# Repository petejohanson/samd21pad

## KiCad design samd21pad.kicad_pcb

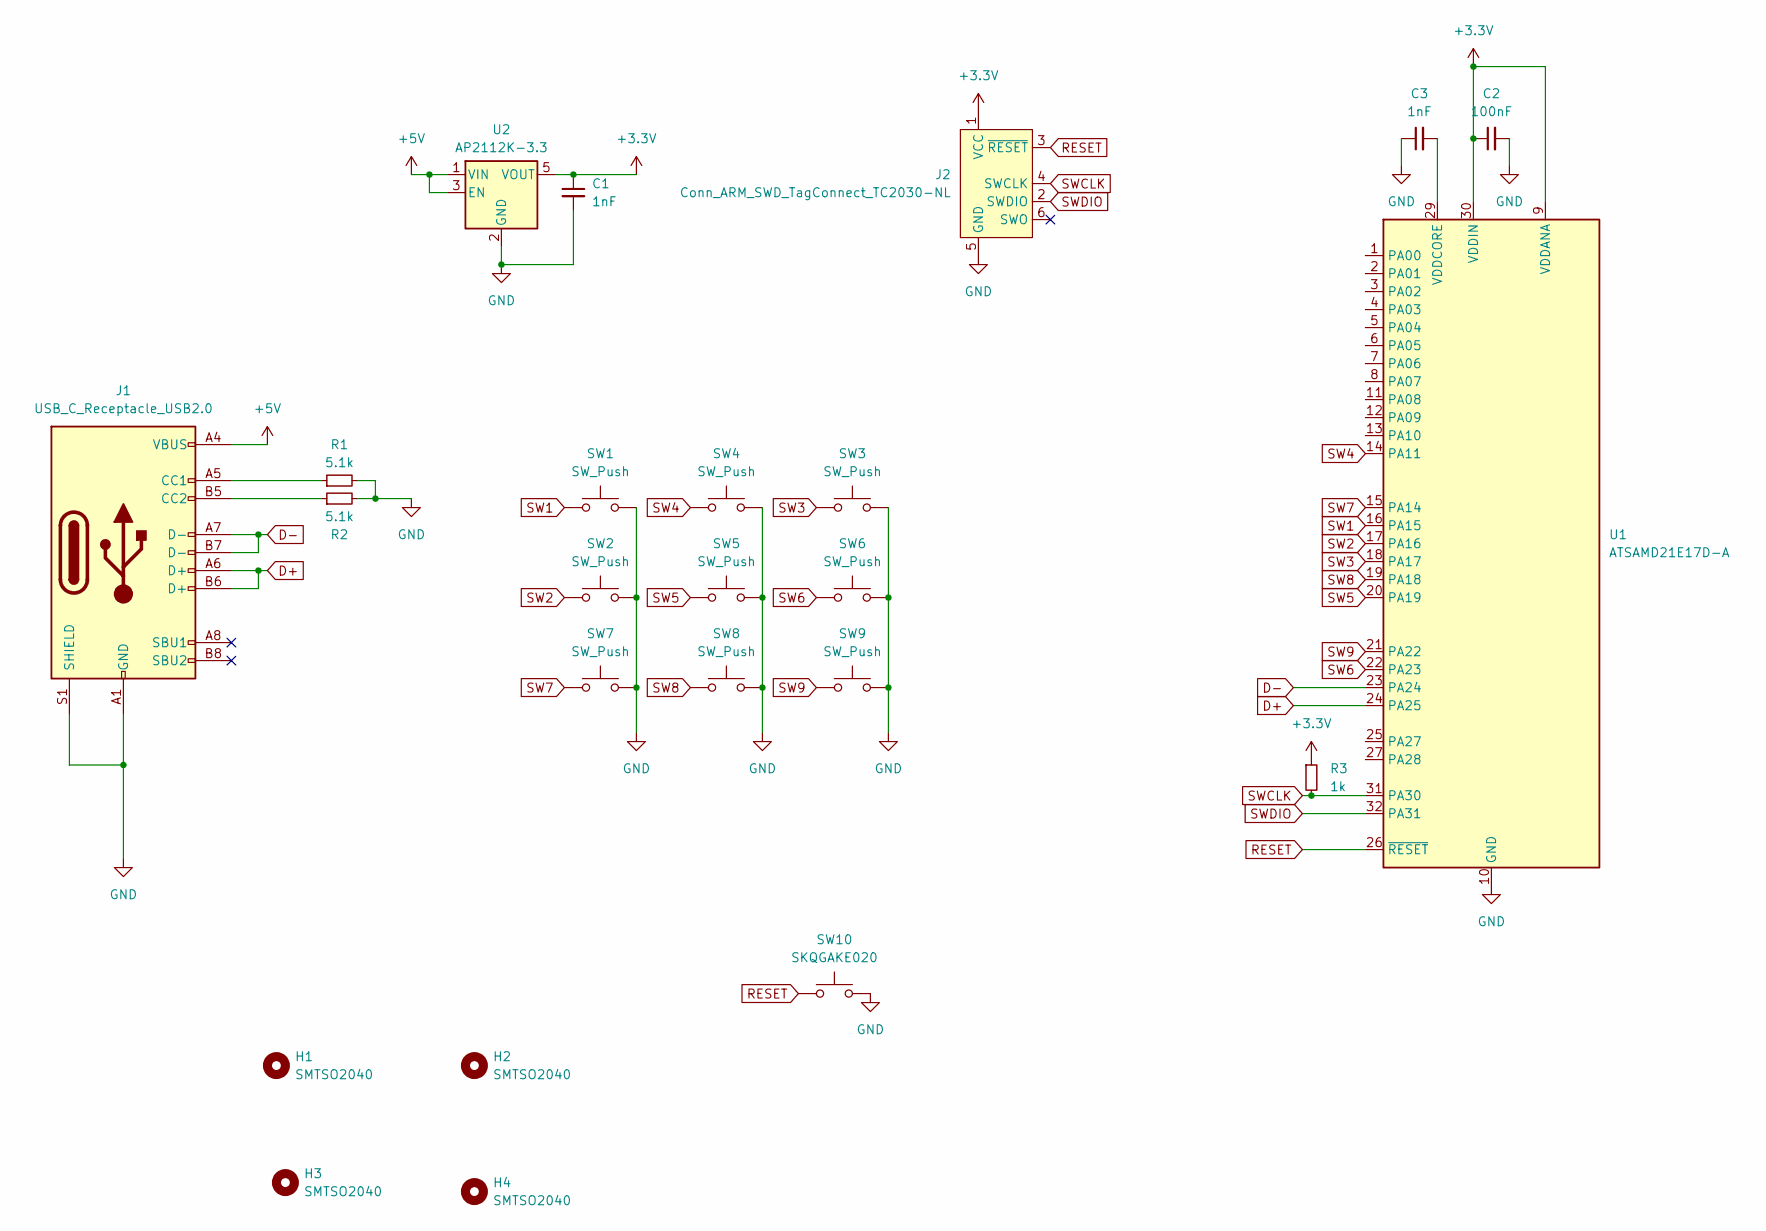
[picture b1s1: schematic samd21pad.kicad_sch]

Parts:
C1, C3: 1nF; C_0805_2012Metric; LCSC Part Number C129637
C2: 100nF; C_0805_2012Metric; LCSC Part Number C2169363
H1, H2, H3, H4: SMTSO2040; MountingHole_M2_Pad_NonPTH_TopOnly; LCSC Part Number C2916349
J1: USB_C_Receptacle_USB2.0; USB_C_Receptacle_GT-USB-7010; LCSC Part Number C3001293
J2: Conn_ARM_SWD_TagConnect_TC2030-NL; Tag-Connect_TC2030-IDC-NL_2x03_P1.27mm_Vertical
R1, R2: 5.1k; R_0805_2012Metric
R3: 1k; R_0805_2012Metric
SW1, SW2, SW3, SW4, SW5, SW6, SW7, SW8, SW9: SW_Push; SW_MX_1u
SW10: SKQGAKE020; SW_SPST_SKQG_WithStem; MPN SKQGAKE020; LCSC Part Number C388858
U1: ATSAMD21E17D-A; TQFP-32_7x7mm_P0.8mm; MPN ATSAMD21E17D-A
U2: AP2112K-3.3; SOT-23-5; MPN AP2112K-3.3; LCSC Part Number C3021085

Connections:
+3.3V: C1.1, C2.1, J2.1 (VCC), R3.1, U1.9 (VDDANA), U1.30 (VDDIN), U2.5 (VOUT)
+5V: J1.A4 (VBUS), J1.A9 (VBUS), J1.B4 (VBUS), J1.B9 (VBUS), U2.1 (VIN), U2.3 (EN)
D+: J1.A6 (D+), J1.B6 (D+), U1.24 (PA25)
D-: J1.A7 (D-), J1.B7 (D-), U1.23 (PA24)
GND: C1.2, C2.2, C3.1, J1.A1 (GND), J1.A12 (GND), J1.B1 (GND), J1.B12 (GND), J1.S1 (SHIELD), J2.5 (GND), R1.2, R2.2, SW1.2, SW2.2, SW3.2, SW4.2, SW5.2, SW6.2, SW7.2, SW8.2, SW9.2, SW10.2, U1.10 (GND), U1.28 (GND), U2.2 (GND)
unnamed: J1.A5 (CC1), R1.1
unnamed: J1.B5 (CC2), R2.1
unnamed: C3.2, U1.29 (VDDCORE)
RESET: J2.3 (~RESET), SW10.1, U1.26 (~RESET)
SW1: SW1.1, U1.16 (PA15)
SW2: SW2.1, U1.17 (PA16)
SW3: SW3.1, U1.18 (PA17)
SW4: SW4.1, U1.14 (PA11)
SW5: SW5.1, U1.20 (PA19)
SW6: SW6.1, U1.22 (PA23)
SW7: SW7.1, U1.15 (PA14)
SW8: SW8.1, U1.19 (PA18)
SW9: SW9.1, U1.21 (PA22)
SWCLK: J2.4 (SWCLK), R3.2, U1.31 (PA30)
SWDIO: J2.2 (SWDIO), U1.32 (PA31)

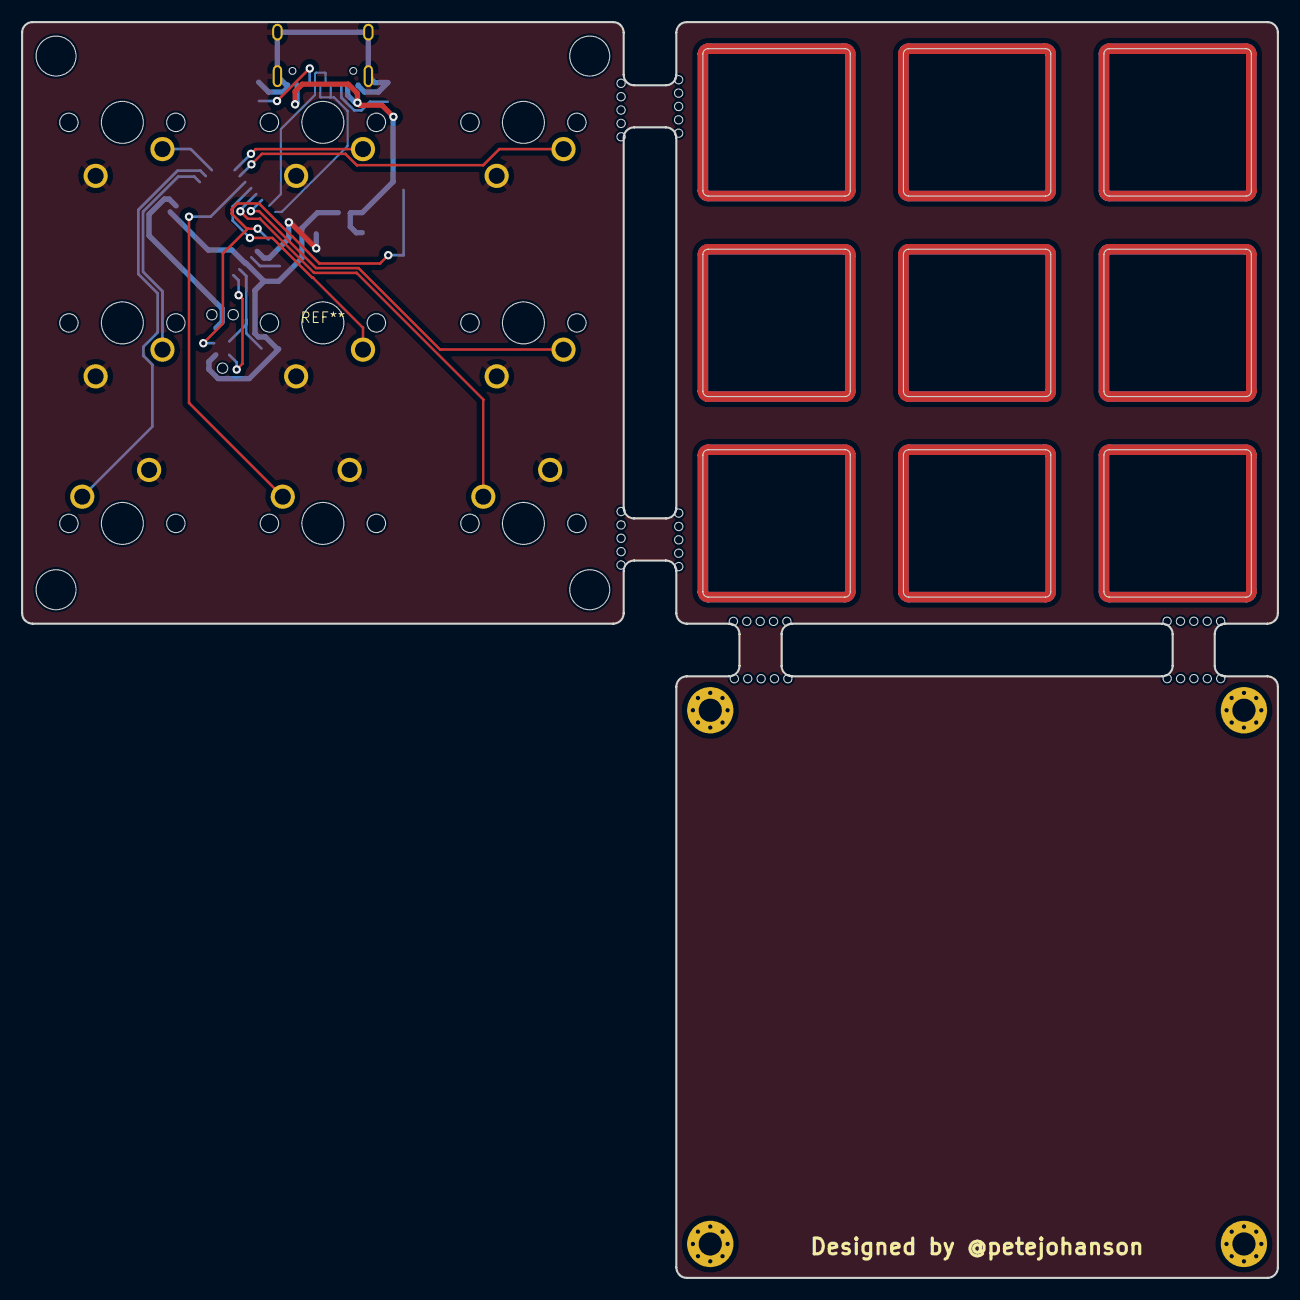
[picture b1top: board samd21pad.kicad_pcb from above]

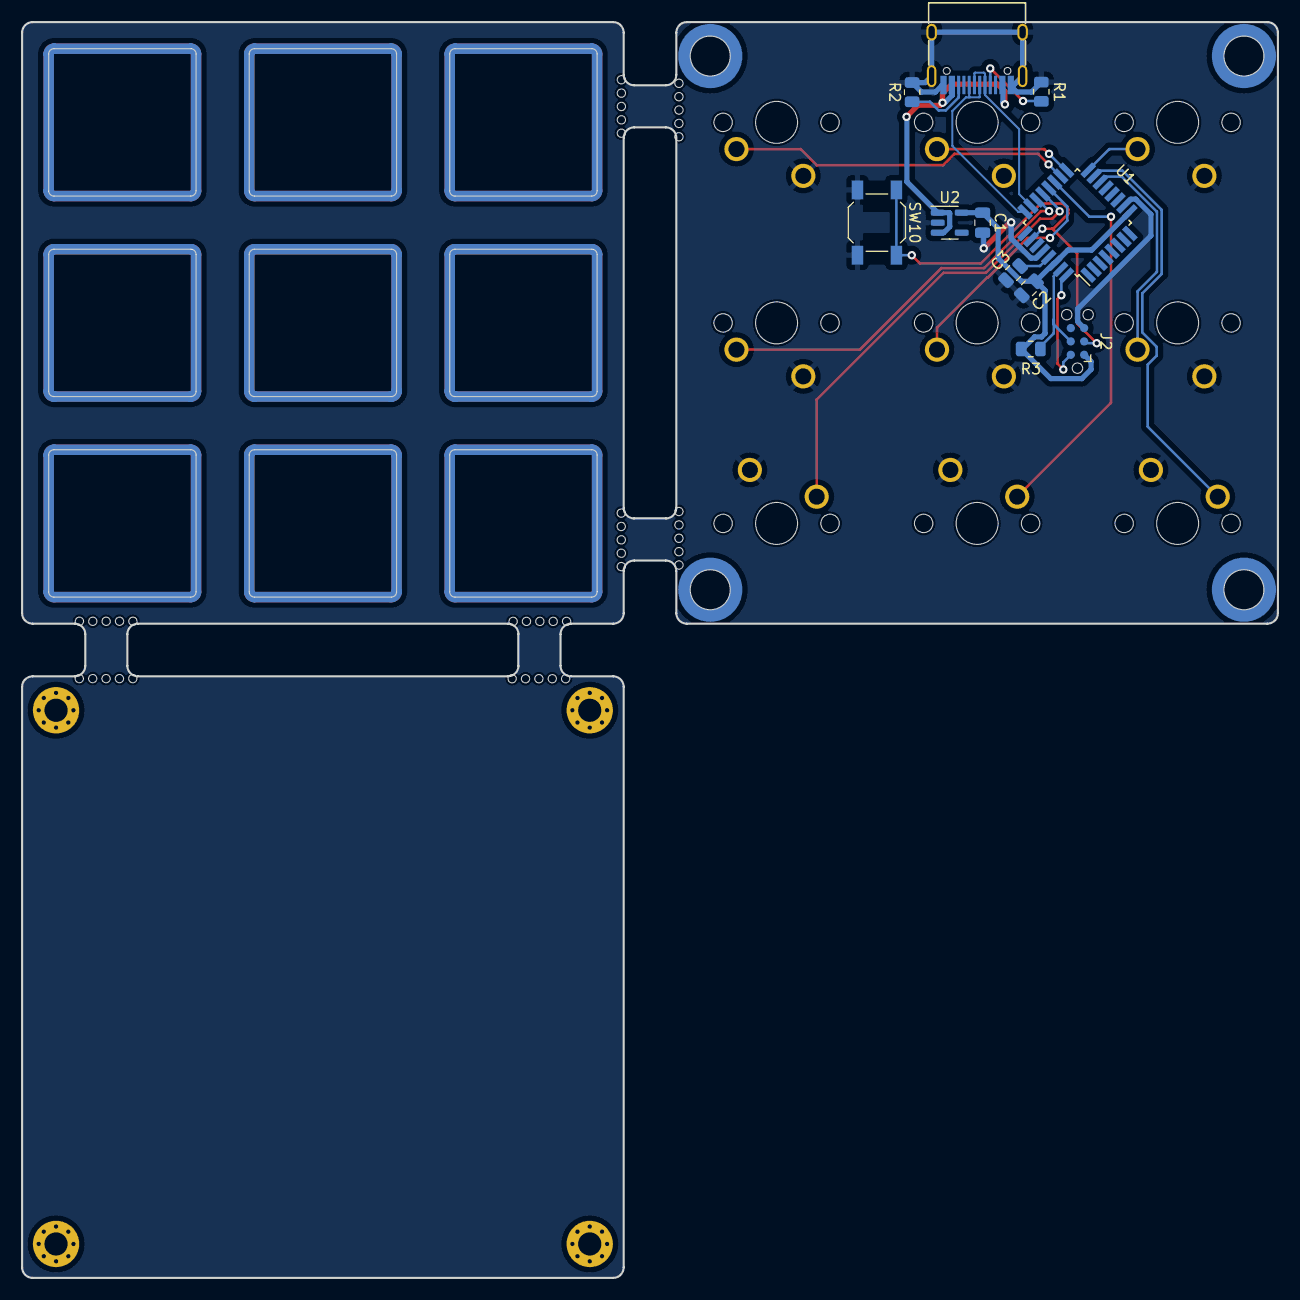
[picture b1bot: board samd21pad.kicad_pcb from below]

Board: 2 copper layers, 119.3 x 119.3 mm, 24 parts (15 on the bottom side), 20 nets.

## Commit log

2023-07-04 Initial revision.
2023-07-05 3-piece assembly edge cuts, mounting holes, plate, and silk fixes.
2023-07-05 Add export automation.
2023-07-05 Add LICENSE.
2023-07-05 CI export fix.
2023-07-05 BOM fixes.
2023-07-08 Add silk for the bottom plate for the SMK meetup.
2023-07-08 General routing clean ups, silk tweaks, etc.
2023-07-28 Fix the bottom plate hole locations to align with solder nuts.
2023-07-28 Fix the solder nut part/JLC number.
2023-12-05 Tweaks for USB shield handling, nuke meetup silk.
2023-12-05 JLC KiBot fixes.
2023-12-05 Assembly J1 USB port.
